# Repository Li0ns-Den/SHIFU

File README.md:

# SHIFU: Sensing Heat & Intense Fluid Uh-ohs
Data acquisition system for combined fluid temperature and pressure

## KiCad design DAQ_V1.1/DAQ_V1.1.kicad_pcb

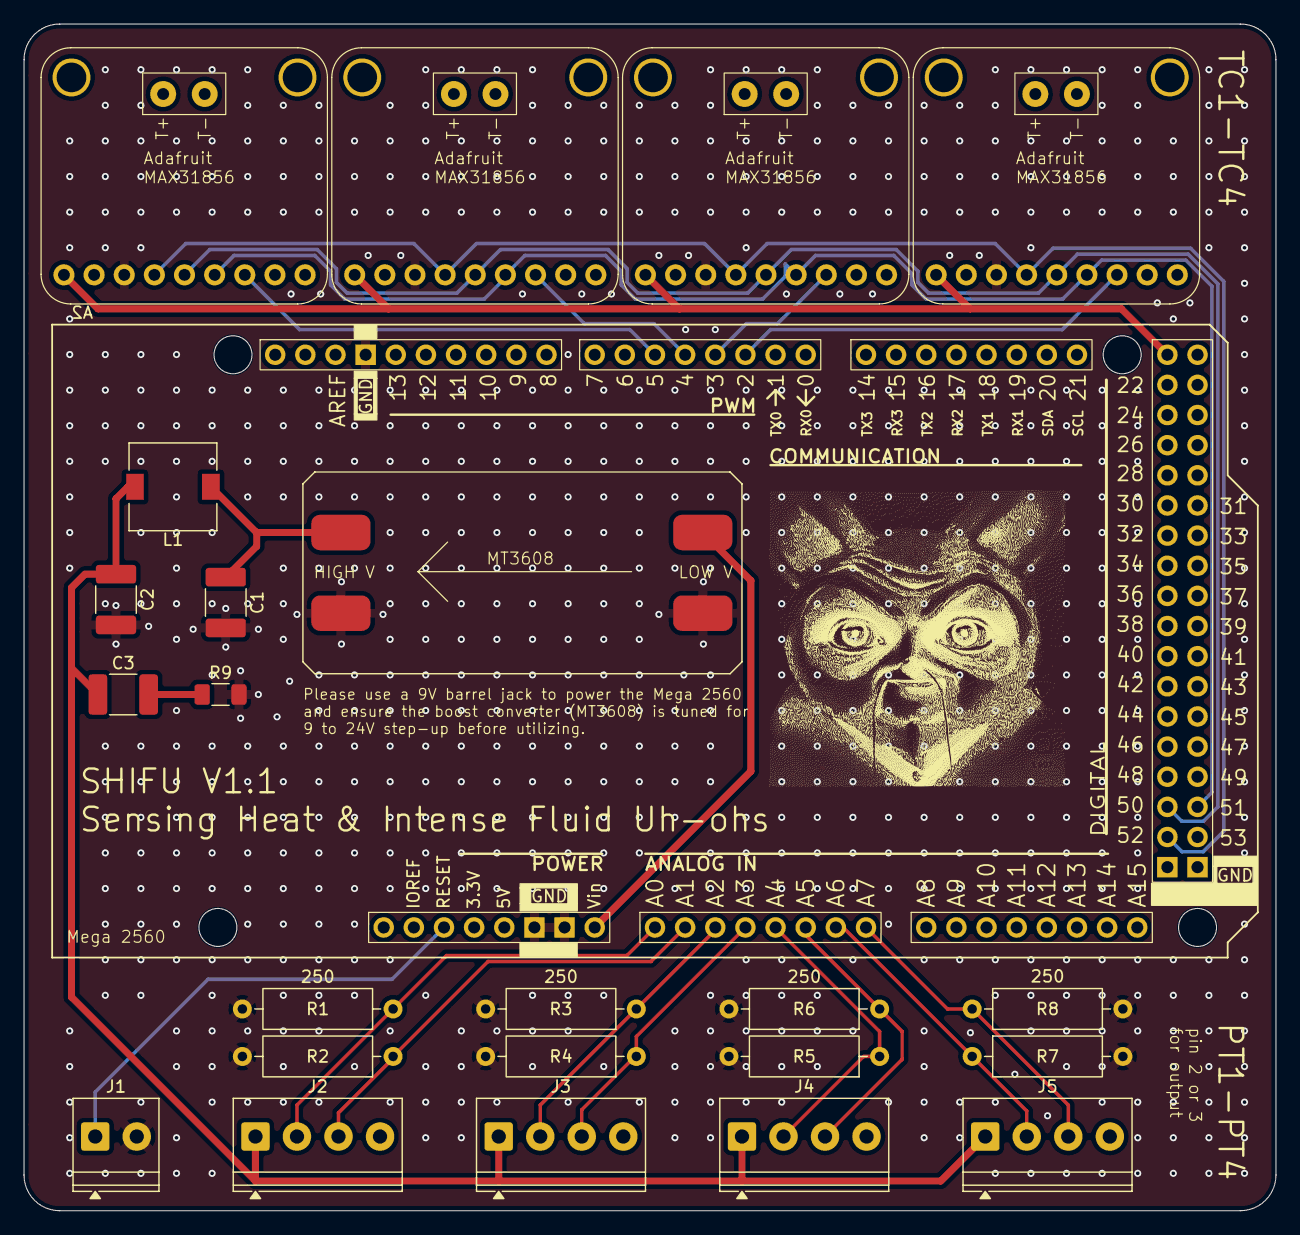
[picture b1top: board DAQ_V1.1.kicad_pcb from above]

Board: 4 copper layers, 105.5 x 100.0 mm, 24 parts (0 on the bottom side), 22 nets.

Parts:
A2: Arduino_Mega2560_R3_Shield; Arduino_Mega2560_R3_Shield_custom
C1: 22u; C_1812_4532Metric_Pad1.57x3.40mm_HandSolder
C2: 10u; C_1812_4532Metric_Pad1.57x3.40mm_HandSolder
C3: 47u; C_1812_4532Metric_Pad1.57x3.40mm_HandSolder
J1: Screw_Terminal_01x02; TerminalBlock_Phoenix_PT-1,5-2-3.5-H_1x02_P3.50mm_Horizontal
J2, J3, J4, J5: Screw_Terminal_01x04; TerminalBlock_Phoenix_PT-1,5-4-3.5-H_1x04_P3.50mm_Horizontal
L1: 10u; L_7.3x7.3_H3.5
R1, R2, R3, R4, R5, R6, R7, R8: 250; R_Axial_DIN0309_L9.0mm_D3.2mm_P12.70mm_Horizontal
R9: R; R_1206_3216Metric_Pad1.30x1.75mm_HandSolder
U1, U2, U3, U4: Max31856Pads
U5: hw-045

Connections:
GND: A2.GND1 (GND), A2.GND2 (GND), A2.GND3 (GND), C1.2, C2.2, J1.2, R1.2, R2.2, R3.2, R4.2, R5.2, R6.2, R7.2, R8.2, R9.2, U1.3 (GND), U2.3 (GND), U3.3 (GND), U4.3 (GND), U5.2 (Vin-), U5.4 (Vout-)
unnamed: A2.D2 (D2_INT0), U4.7 (CS)
unnamed: A2.D3 (D3_INT1), U3.7 (CS)
unnamed: A2.D50 (D50_MISO), U1.5 (SDO), U2.5 (SDO), U3.5 (SDO), U4.5 (SDO)
unnamed: A2.D51 (D51_MOSI), U1.6 (SDI), U2.6 (SDI), U3.6 (SDI), U4.6 (SDI)
unnamed: A2.D52 (D52_SCK), U1.4 (SCK), U2.4 (SCK), U3.4 (SCK), U4.4 (SCK)
unnamed: A2.RST1 (RESET), J1.1
unnamed: C3.2, R9.1
unnamed: C2.1, C3.1, J2.1, J3.1, J4.1, J5.1, L1.2
unnamed: A2.A0, J2.2, R1.1
unnamed: A2.A1, J2.3, R2.1
unnamed: A2.A2, J3.2, R3.1
unnamed: A2.A3, J3.3, R4.1
unnamed: A2.A4, J4.2, R5.1
unnamed: A2.A5, J4.3, R6.1
unnamed: A2.A6, J5.2, R7.1
unnamed: A2.A7, J5.3, R8.1
unnamed: A2.D5, U1.7 (CS)
unnamed: A2.5V3 (5V), U1.1 (Vin), U2.1 (Vin), U3.1 (Vin), U4.1 (Vin)
unnamed: A2.D4, U2.7 (CS)
unnamed: A2.VIN, U5.1 (Vin+)
unnamed: C1.1, L1.1, U5.3 (Vout+)
